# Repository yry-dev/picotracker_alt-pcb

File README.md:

# Picotracker Alt-PCB

~~**Do not fabricate! There could be a major mistake around MIDI!!**~~

**[Alex fixed it!](https://github.com/ijnekenamay/picotracker_alt-pcb/pull/2) We should be able to go ahead with production now.**

This project is about [democloid picoTracker's](https://github.com/democloid/picoTracker/) alternative PCB.
Inexpensive handheld devices can be built to run LittleGPTracker(a.k.a piggytracker).
It basically follows the original DIY version, with a few modifications of my own. They are described below.

[You can see it in motion here.](https://www.instagram.com/p/C2BvngaruZN/?utm_source=ig_web_copy_link&igsh=MzRlODBiNWFlZA==)

## Feature

- The two PCBs act as an enclosure by sandwiching the components together.
- I wanted a module for the charging function and plenty of memory, so I went with the [Pimoroni Pico LiPo](https://shop.pimoroni.com/products/pimoroni-pico-lipo).
- I wanted a micro-speaker like the DirtywaveM8, so I added one... and a Class D amplifier module.
- A speaker kill switch has been added.
- This also uses Kailh Choc V1 for the keycaps because of my personal taste.
- You can change any specification by yourself if you have access to Kicad.
- [See image for values of components around MIDI.](https://raw.githubusercontent.com/ijnekenamay/picotracker_alt-pcb/main/images/MIDI_resistor_value.jpg)
- I designed a back panel that could be output with a 3D printer because I felt the microspeaker needed box resonance. Also, if you would like to try it, please see the STL data. Feedback is welcome.
- 

## BOM

| Value | Qty | Avg unit price¹ | Mouser | DigiKey | Notes |
| --- | --- | --- | --- | --- | --- |
| Pimoroni Pico LiPo 16MB | 1 | ~$8–16 | — | — | [Pimoroni](https://shop.pimoroni.com/products/pimoroni-pico-lipo) (~$15.95, [PiShop US](https://www.pishop.us/product/pimoroni-pico-lipo-16mb/)) · [JP](https://akizukidenshi.com/catalog/g/g116997/). Equivalent: [Waveshare RP2040-Plus 16MB](https://www.amazon.com/Waveshare-RP2040-Plus-High-Performance-Microcontroller-Compatible/dp/B09KZKKWJT) ([Waveshare](https://www.waveshare.com/rp2040-plus.htm)), ~$8 — Pico-pinout, USB-C, onboard LiPo charge, 16MB (use the **no-header/castellated** version). |
| ILI9341 3.2" display | 1 | ~$12–18 | — | — | [AliExpress](https://www.aliexpress.us/item/3256802819098352.html). Equivalents: generic 3.2" ILI9341 SPI 320×240 on [Amazon](https://www.amazon.com/ALMOCN-ILI9341-Display-320x240-Screen/dp/B0C88S6FK7) (ALMOCN/Hosyond/ACEIRMC, ~$15) — **verify the 8-pin SPI header order matches J7**. Tayda has only a [2.8" ILI9341](https://www.taydaelectronics.com/2-8-inch-spi-display-screen-tft-with-touch-ili9341.html) (smaller). Mouser/DigiKey carry ILI9341 breakouts (Adafruit/Newhaven) but with different pinouts — **not drop-in**. |
| GY-PCM5102 DAC module | 1 | — | — | — | [AliExpress](https://www.aliexpress.us/item/3256802711963831.html) |
| Adafruit Micro SD SPI/SDIO Breakout | 1 | — | — | — | [Adafruit](https://www.adafruit.com/product/4682) |
| Kailh Choc V1 key switch | 9 | — | — | — | specialty (mechanical-keyboard vendors) |
| keycaps (Kailh Choc) | 9 | — | — | — | specialty |
| MAX98306 class-D amp module | 1 | — | — | — | [AliExpress](https://ja.aliexpress.com/item/1005004990814956.html) (Adafruit #987) |
| Micro speaker | 2 | — | — | — | [Akizuki](https://akizukidenshi.com/catalog/g/gP-12494/) |
| DPDT slide switch (through-hole) | 1 | ~$0.84 | [JS202011AQN](https://www.mouser.com/c/?q=JS202011AQN) | [JS202011AQN](https://www.digikey.com/en/products/detail/c-k/JS202011AQN/1640096) | J9 (KILL_SWITCH); C&K JS202011AQN, right-angle. Generic SS-22 / MSK22D18G2 (LCSC C2906279, ~$0.07) also fits. GND on center pins. |
| PJ-311 3.5mm stereo jack | 2 | varies | — | — | MIDI in/out (J1, J2). Generic PJ-311/PJ-320 import — no footprint-compatible Mouser/DigiKey catalog part. |
| 1N4148 | 1 | ~$0.10 | [1N4148](https://www.mouser.com/c/?q=1N4148) | [1N4148](https://www.digikey.com/en/products/result?keywords=1N4148) | D1; DO-35 axial |
| 47R | 2 | ~$0.11 | [CFR-25JB-52-47R](https://www.mouser.com/c/?q=CFR-25JB-52-47R) | [CFR-25JB-52-47R](https://www.digikey.com/en/products/result?keywords=CFR-25JB-52-47R) | axial 1/4W (DIN0207, 7.62mm) |
| 220R | 1 | ~$0.10 | [CFR-25JB-52-220R](https://www.mouser.com/c/?q=CFR-25JB-52-220R) | [CFR-25JB-52-220R](https://www.digikey.com/en/products/result?keywords=CFR-25JB-52-220R) | axial 1/4W (DIN0207, 7.62mm) |
| 470R | 1 | ~$0.11 | [CFR-25JB-52-470R](https://www.mouser.com/c/?q=CFR-25JB-52-470R) | [CFR-25JB-52-470R](https://www.digikey.com/en/products/result?keywords=CFR-25JB-52-470R) | axial 1/4W (DIN0207, 7.62mm) |
| 10k | 1 | ~$0.10 | [CFR-25JB-52-10K](https://www.mouser.com/c/?q=CFR-25JB-52-10K) | [CFR-25JB-52-10K](https://www.digikey.com/en/products/result?keywords=CFR-25JB-52-10K) | axial 1/4W (DIN0207, 7.62mm) |
| 6N138 | 1 | ~$0.83 | [6N138](https://www.mouser.com/c/?q=6N138) | [6N138](https://www.digikey.com/en/products/result?keywords=6N138) | U2; DIP-8 optocoupler |
| LiPo battery | 1 | — | — | — | 1200mAh (author's choice) — hobby battery vendors |
| Pin headers / standoffs / screws / nuts | * | — | [headers](https://www.mouser.com/c/?q=2.54mm+pin+header) | [headers](https://www.digikey.com/en/products/result?keywords=2.54mm+pin+header) | See note below on short headers vs sockets |

¹ **Avg unit price** — indicative qty-1 price in USD, from Mouser (the DPDT switch is averaged with DigiKey). Modules are priced at their linked vendors (they aren't stocked by Mouser/DigiKey). Most distributor cells are keyword/site searches — pick the exact package/stock on the results page; the DPDT switch uses direct product links (Mouser and DigiKey). Stock and prices change, so confirm at the link before ordering.

It is recommended to use short pin headers and to solder directly without using sockets. At the very least, the effective depth of the 3D printer back panel is only 11 mm, which would interfere with the use of pin sockets. (but i wanted to go thin)

The images below are prototype versions and differ from the actual data.

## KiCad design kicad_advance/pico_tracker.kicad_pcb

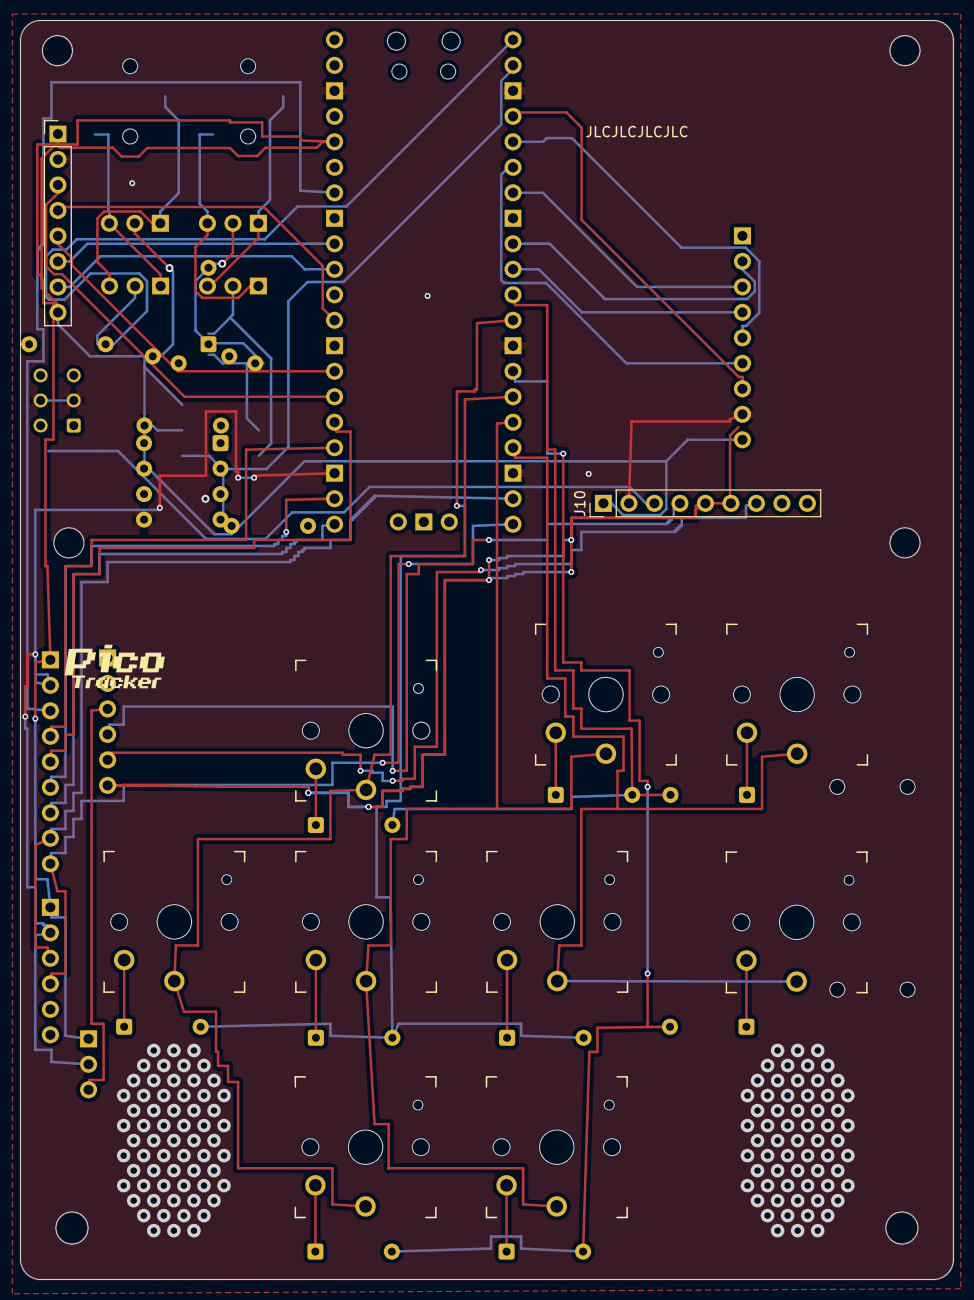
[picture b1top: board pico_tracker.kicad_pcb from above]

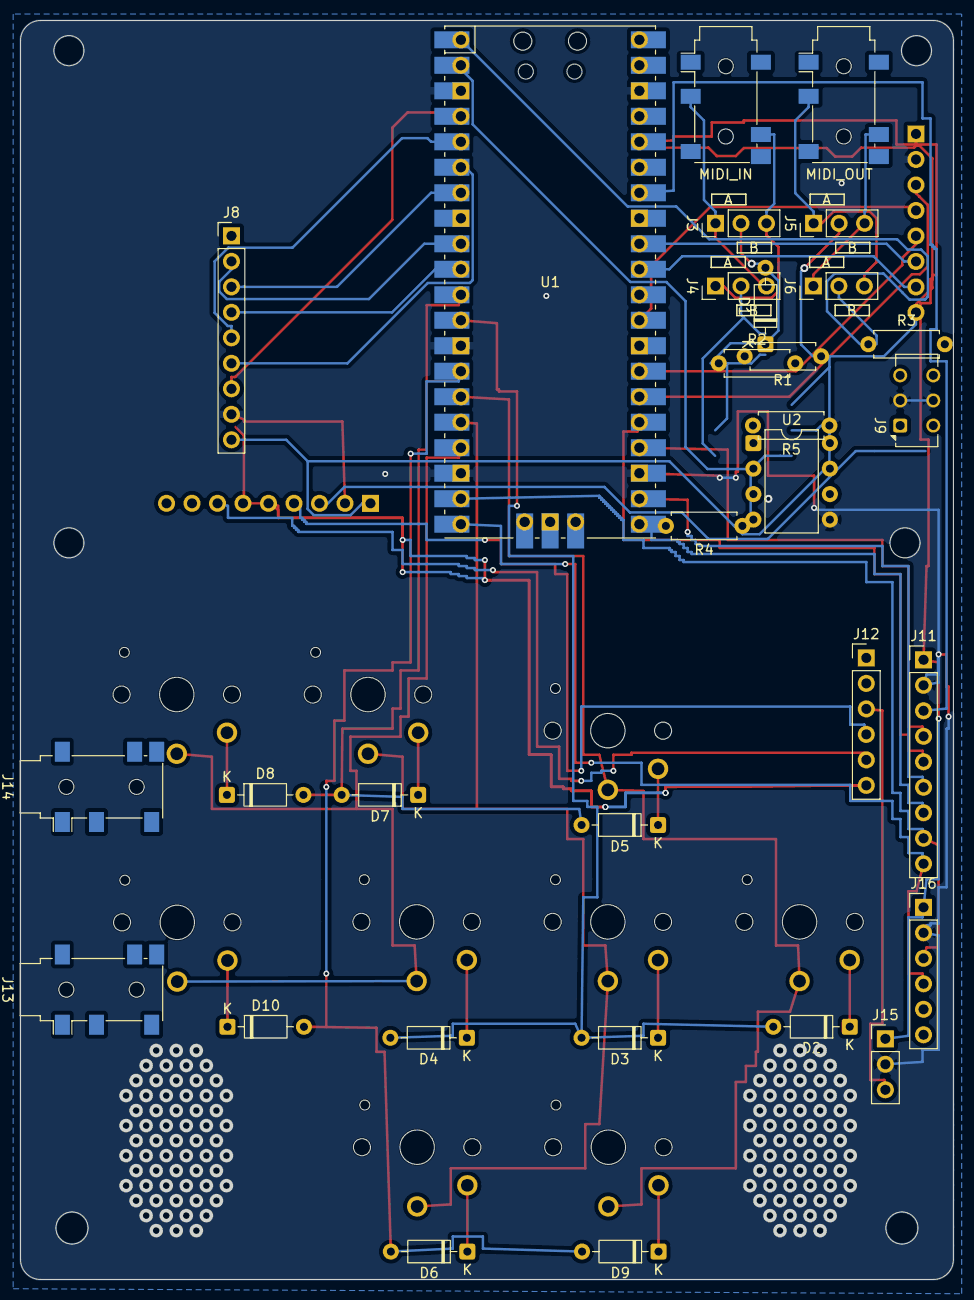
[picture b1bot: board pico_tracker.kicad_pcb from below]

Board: 2 copper layers, 92.9 x 125.4 mm, 43 parts (31 on the bottom side), 52 nets.

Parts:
D1, D2, D3, D4, D5, D6, D7, D8, D9, D10: 1n4148; D_DO-35_SOD27_P7.62mm_Horizontal
G1: LOGO; logo_silk
J1: MIDI_OUT; Jack_3.5mm_PJ311_Horizontal
J2: MIDI_IN; Jack_3.5mm_PJ311_Horizontal
J3: MIDI_IN_A_B_VCC; PinHeader_1x03_P2.54mm_Vertical
J4: MIDI_IN_A_B_DATA; PinHeader_1x03_P2.54mm_Vertical
J5: MIDI_OUT_A_B_VCC; PinHeader_1x03_P2.54mm_Vertical
J6: MIDI_OUT_A_B_DATA; PinHeader_1x03_P2.54mm_Vertical
J7: DISPLAY; PinHeader_1x08_P2.54mm_Vertical
J8: SDCARD; PinHeader_1x09_P2.54mm_Vertical
J9: KILL_SWITCH; SW_CK_JS202011AQN_DPDT_Angled
J10: DclassAMP; PinHeader_1x09_P2.54mm_Vertical
J11: CODEC_DIG; PinHeader_1x09_P2.54mm_Vertical
J12: CODEC_ANA; PinHeader_1x06_P2.54mm_Vertical
J13: LINE_IN; Jack_3.5mm_PJ311_Horizontal
J14: PHONES; Jack_3.5mm_PJ311_Horizontal
J15: MIC_MODULE; PinHeader_1x03_P2.54mm_Vertical
J16: FUEL_GAUGE; PinHeader_1x06_P2.54mm_Vertical
R1, R3: 47R; R_Axial_DIN0207_L6.3mm_D2.5mm_P7.62mm_Horizontal
R2: 220R; R_Axial_DIN0207_L6.3mm_D2.5mm_P7.62mm_Horizontal
R4: 470R; R_Axial_DIN0207_L6.3mm_D2.5mm_P7.62mm_Horizontal
R5: 10k; R_Axial_DIN0207_L6.3mm_D2.5mm_P7.62mm_Horizontal
SW1, SW2, SW3, SW4, SW5, SW6, SW7, SW8, SW9: SW_PG1350
U1: Pico; RPi_Pico_SMD_TH
U2: 6N138; DIP-8_W7.62mm

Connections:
AGND: J10.5, J10.6, J12.6
BCK: J11.4, U1.24 (GPIO18)
CLK: J8.7, U1.4 (GPIO2)
COL0: SW1.1, SW4.1, SW8.1, U1.15 (GPIO11)
COL1: SW2.1, SW5.1, SW6.1, U1.16 (GPIO12)
COL2: SW3.1, SW7.1, SW9.1, U1.17 (GPIO13)
D1: J8.3, U1.7 (GPIO5)
D3: J8.4, U1.10 (GPIO7)
DAT2: J8.2, U1.9 (GPIO6)
DIN: J11.6, U1.22 (GPIO17)
DP3: J7.3, U1.26 (GPIO20)
DP4: J7.4, U1.29 (GPIO22)
DP5: J7.5, U1.27 (GPIO21)
DP6: J7.6, U1.32 (GPIO27_ADC1)
DP7: J7.7, U1.31 (GPIO26_ADC0)
GND: J7.2, J8.8, J9.2, J9.5, J10.2, J11.2, J15.2, J16.2, R5.1, U1.3 (GND), U1.13 (GND), U1.18 (GND), U1.23 (GND), U1.38 (GND), U2.5
I2S_SDIN: J11.7, U1.21 (GPIO16)
KILL_SWITCH: J9.1, J9.4, J10.3
LRCK: J11.5, U1.25 (GPIO19)
L_AMP: J10.4, J12.4
MCLK: J11.3, U1.34 (GPIO28_ADC2)
MIC_IN: J12.3, J15.3
unnamed: D1.2, J4.2, U2.3
unnamed: D1.1, R2.2, U2.2
unnamed: D2.1, SW1.2
unnamed: D3.1, SW2.2
unnamed: D4.1, SW3.2
unnamed: D5.1, SW4.2
unnamed: D6.1, SW5.2
unnamed: D7.1, SW6.2
unnamed: D8.1, SW7.2
unnamed: D9.1, SW8.2
unnamed: D10.1, SW9.2
unnamed: J3.1, J4.3
unnamed: J3.2, R2.1
unnamed: J3.3, J4.1
unnamed: J5.1, J6.3
unnamed: J5.2, R1.2
unnamed: J5.3, J6.1
unnamed: J6.2, R3.2
unnamed: R5.2, U2.7
ROW0: D5.2, D7.2, D8.2, U1.11 (GPIO8)
ROW1: D2.2, D3.2, D4.2, U1.12 (GPIO9)
ROW2: D6.2, D9.2, D10.2, U1.14 (GPIO10)
RX: R4.1, U1.2 (GPIO1), U2.6
R_AMP: J10.7, J12.5
SCL: J11.9, J16.4, U1.20 (GPIO15)
SDA: J11.8, J16.3, U1.19 (GPIO14)
SI: J8.5, U1.5 (GPIO3)
SO: J8.6, U1.6 (GPIO4)
TX: R3.1, U1.1 (GPIO0)
VCC: J7.1, J7.8, J8.9, J10.1, J11.1, J15.1, J16.1, R1.1, R4.2, U1.36 (3V3), U2.8
